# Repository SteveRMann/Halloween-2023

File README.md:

## PrizeDelivery
This repository contains the files for the Halloween prize delivery mechanism.

The mechanism is a rotisserie motor that rotates on command (a button press).
Once started, the motor continues until a "home" microswitch is closed.
Because the motor is slow, like 20 seconds for 360°, the "home" position is 
just before a drop would occur.

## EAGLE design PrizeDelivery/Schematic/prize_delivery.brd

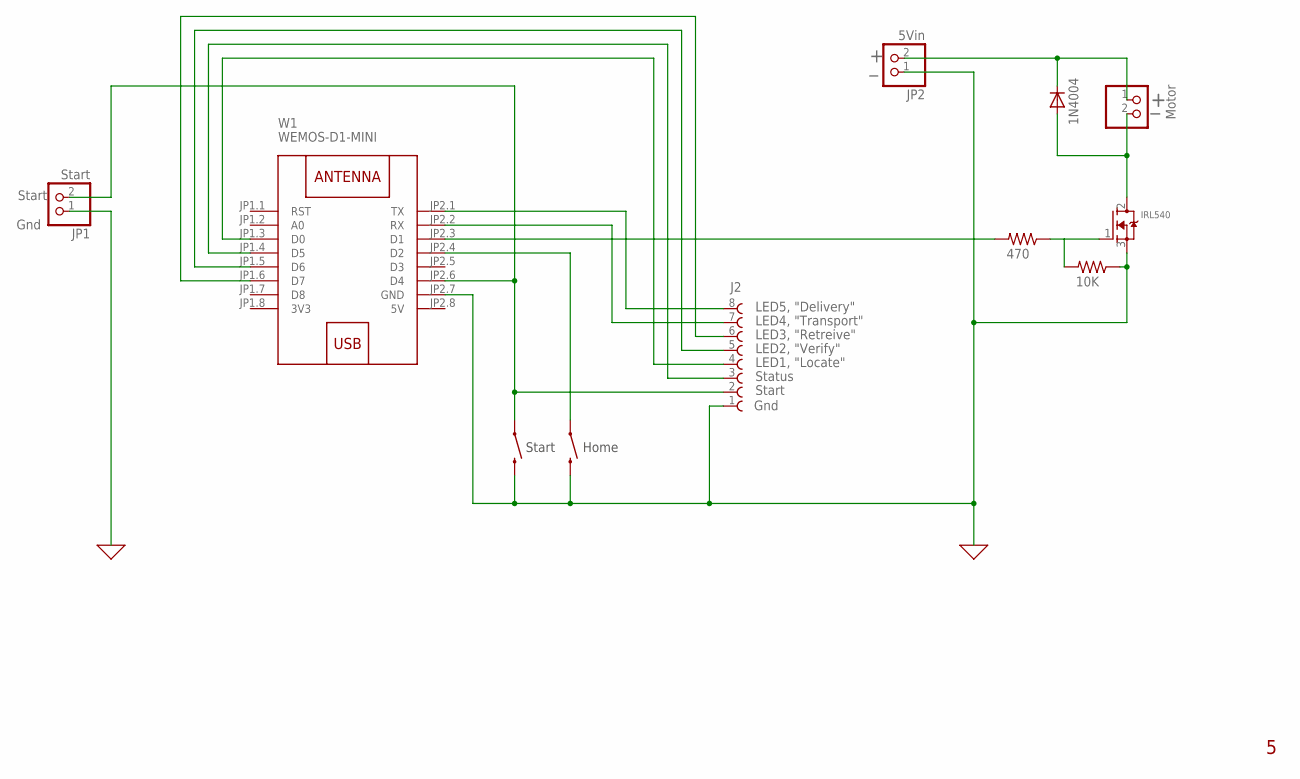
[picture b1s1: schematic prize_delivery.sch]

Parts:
360°: MOMENTARY-SWITCH-SPST-PTH-6.0MM; TACTILE_SWITCH_PTH_6.0MM
D1: 1N4004; DO41-10
J2: 691136710008
JP1: Start; 1X02
JP2: 5Vin; 1X02
JP3: Motor; 1X02
Q1: IRL540; TO220V
R2: 470; 0207/10
R4: 10K; 0207/10
START: MOMENTARY-SWITCH-SPST-PTH-6.0MM; TACTILE_SWITCH_PTH_6.0MM
W1: WEMOS-D1-MINI

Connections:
0: 360°.3 (2), J2.1, JP1.1, JP2.1, Q1.3 (S), R4.1, START.3 (2), W1.JP2.7 (GND)
3V3: W1.JP1.8 (3V3)
5V: W1.JP2.8 (5V)
unnamed: D1.A, JP3.2, Q1.2 (D)
unnamed: D1.C, JP2.2, JP3.1
unnamed: 360°.1, W1.JP2.4 (D2)
unnamed: R2.2, W1.JP2.3 (D1)
unnamed: J2.2, JP1.2, START.1, W1.JP2.6 (D4)
unnamed: Q1.1 (G), R2.1, R4.2
unnamed: J2.4, W1.JP1.3 (D0)
unnamed: J2.5, W1.JP1.5 (D6)
unnamed: J2.6, W1.JP1.6 (D7)
unnamed: J2.8, W1.JP2.1 (TX)
unnamed: J2.7, W1.JP2.2 (RX)
unnamed: J2.3, W1.JP1.4 (D5)

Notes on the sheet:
Home
Start
Gnd
LED1, "Locate"
LED2, "Verify"
LED3, "Retreive"
LED4, "Transport"
LED5, "Delivery"
Status

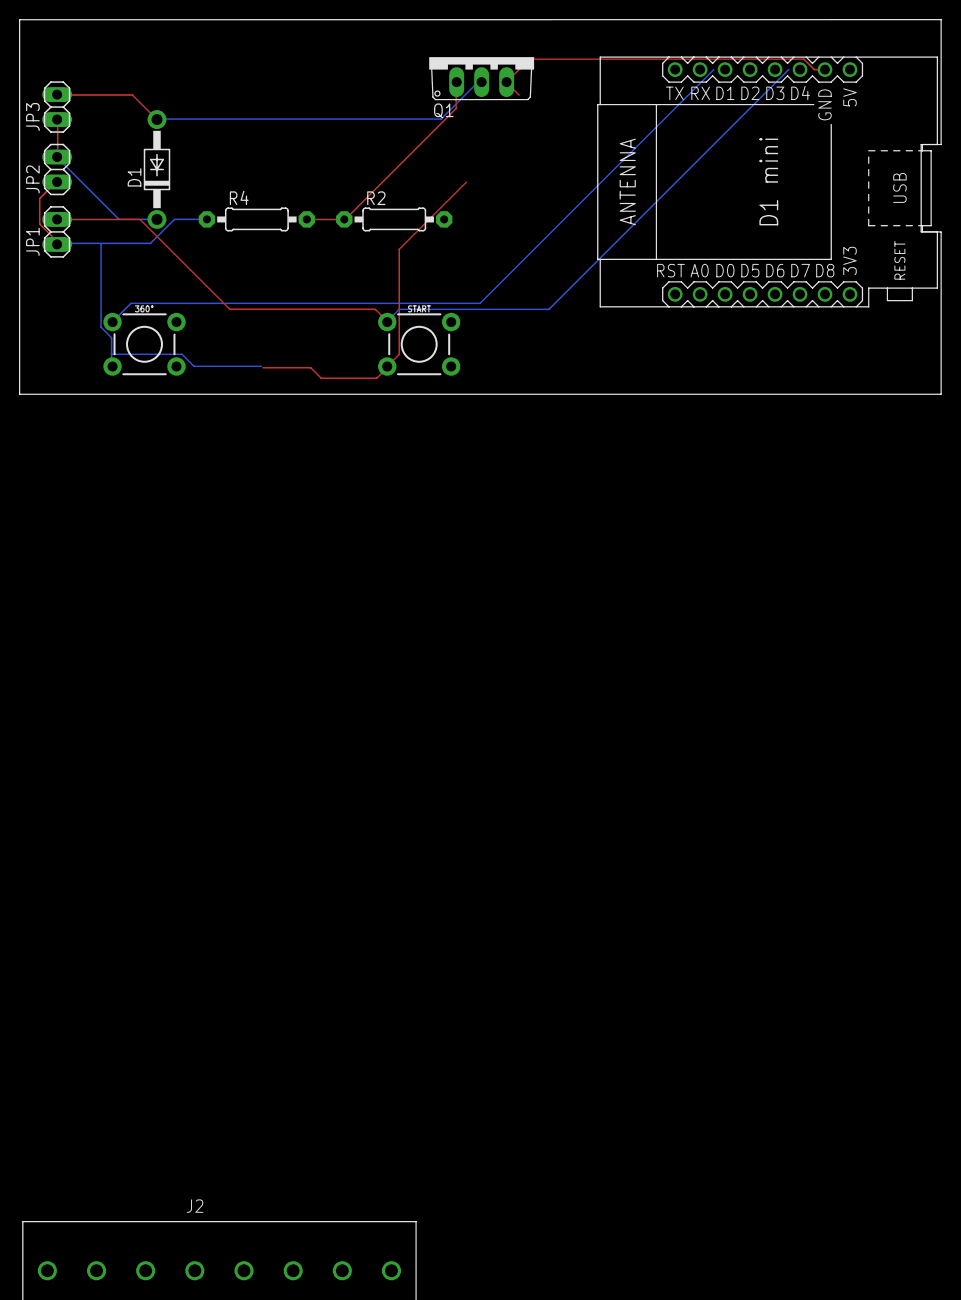
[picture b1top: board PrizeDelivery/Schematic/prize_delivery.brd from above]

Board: 2 copper layers, 93.7 x 38.1 mm, 11 parts (0 on the bottom side), 13 nets.

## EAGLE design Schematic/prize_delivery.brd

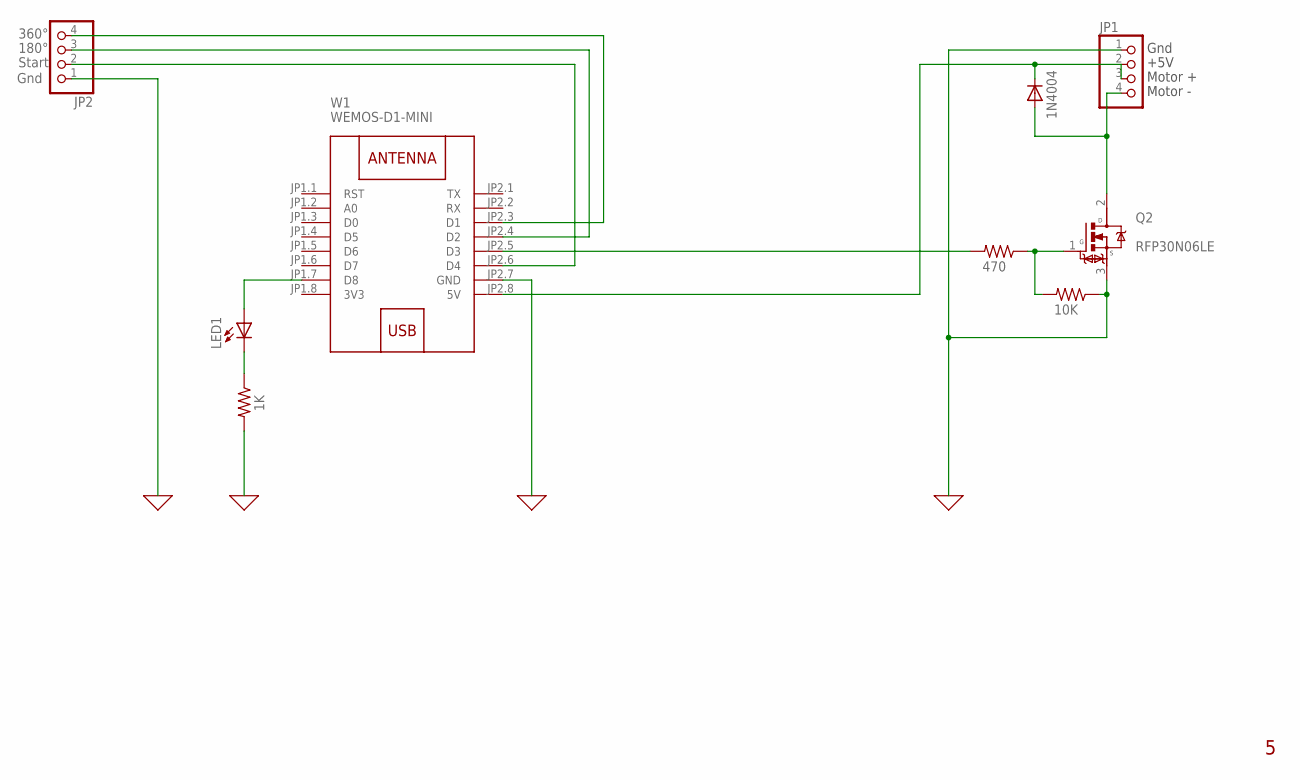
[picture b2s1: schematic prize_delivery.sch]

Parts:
D1: 1N4004; DO41-10
JP1, JP2: PINHD-1X4; 1X04
LED1: LED5MM
Q2: RFP30N06LE; TRANS_RFP30N06LE
R1: 1K; 0207/10
R2: 470; 0207/10
R4: 10K; 0207/10
W1: WEMOS-D1-MINI

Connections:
0: JP1.1, JP2.1, Q2.3 (S), R1.2, R4.1, W1.JP2.7 (GND)
3V3: W1.JP1.8 (3V3)
unnamed: R2.2, W1.JP2.5 (D3)
unnamed: D1.A, JP1.4, Q2.2 (D)
unnamed: D1.C, JP1.2, JP1.3, W1.JP2.8 (5V)
unnamed: JP2.3, W1.JP2.4 (D2)
unnamed: JP2.4, W1.JP2.3 (D1)
unnamed: LED1.A, W1.JP1.7 (D8)
unnamed: LED1.K (C), R1.1
unnamed: Q2.1 (G), R2.1, R4.2
unnamed: JP2.2, W1.JP2.6 (D4)

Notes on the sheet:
Gnd
Start
180°
360°
Motor +
Motor -
+5V

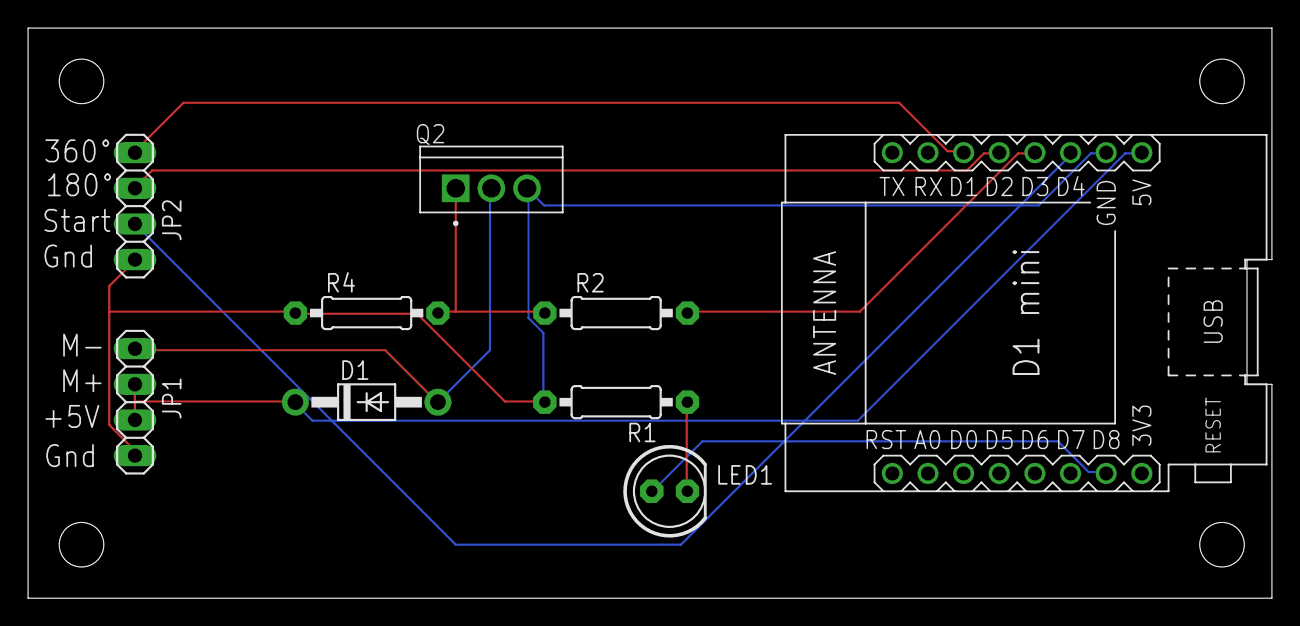
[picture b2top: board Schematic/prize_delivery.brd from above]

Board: 2 copper layers, 88.6 x 40.6 mm, 9 parts (0 on the bottom side), 10 nets.

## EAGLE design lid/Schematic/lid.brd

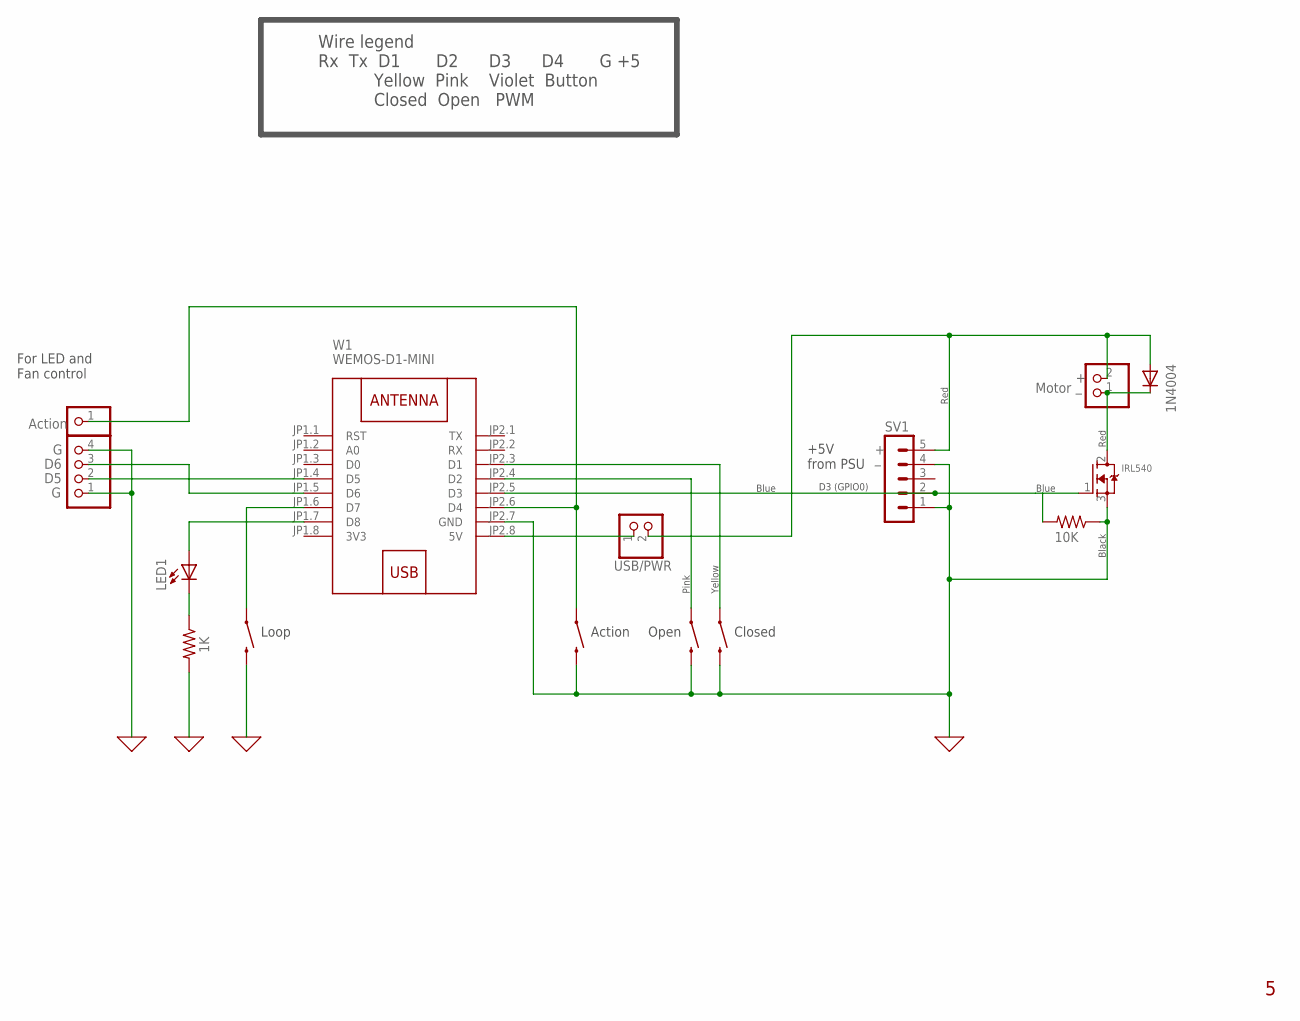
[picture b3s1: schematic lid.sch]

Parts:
ACTION, ACTION1: MOMENTARY-SWITCH-SPST-PTH-6.0MM; TACTILE_SWITCH_PTH_6.0MM
D1: 1N4004; DO41-10
JP1: PINHD-1X1; 1X01
JP3: PINHD-1X2; 1X02
JP4: PINHD-1X4; 1X04
LED1: LED5MM
Q1: IRL540; TO220V
R1: 1K; 0207/10
R4: 10K; 0207/10
S1, S2: MOMENTARY-SWITCH-SPST-PTH-6.0MM; TACTILE_SWITCH_PTH_6.0MM
SV1: MA05-1
USB/PWR: PINHD-1X2; 1X02
W1: WEMOS-D1-MINI

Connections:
0: ACTION.3 (2), ACTION1.3 (2), JP4.1, JP4.4, Q1.3 (S), R1.2, R4.1, S1.3 (2), S2.3 (2), SV1.1, SV1.4, W1.JP2.7 (GND)
3V3: W1.JP1.8 (3V3)
unnamed: Q1.1 (G), R4.2, SV1.2, W1.JP2.5 (D3)
unnamed: D1.C, JP3.1, Q1.2 (D)
unnamed: D1.A, JP3.2, SV1.5, USB/PWR.2
unnamed: S1.1, W1.JP2.4 (D2)
unnamed: S2.1, W1.JP2.3 (D1)
unnamed: LED1.A, W1.JP1.7 (D8)
unnamed: LED1.K (C), R1.1
unnamed: USB/PWR.1, W1.JP2.8 (5V)
unnamed: ACTION.1, JP1.1, W1.JP2.6 (D4)
unnamed: JP4.2, W1.JP1.4 (D5)
unnamed: JP4.3, W1.JP1.5 (D6)
unnamed: ACTION1.1, W1.JP1.6 (D7)

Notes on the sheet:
Motor
+5V from PSU
D3 (GPIO0)
Open
Closed
Yellow
Pink
Blue
Black
Red
Action
Wire legend Rx Tx D1 D2 D3 D4 G +5 Yellow Pink Violet Button Closed Open PWM
For LED and Fan control
Loop

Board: 2 copper layers, 15 parts (0 on the bottom side), 13 nets, no tracks yet.

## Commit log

2023-06-13 New repository
2023-06-14 Cleaning up filenames
2023-06-14 Removed lid
2023-06-15 Commented out mqtt stuff
2023-06-15 Lots of rewtire
2023-06-16 Update schematic
2023-06-16 Crap
2023-06-17 Pause at 180 then continue to 360.
2023-06-17 Modified schematic
2023-06-17 Update PCB
2023-06-18 Cleanup
2023-06-18 Bumped start_button debounce to 300ms
2023-06-19 Added ESPHome yaml file
2023-06-20 Switch hardware to D1 Mini Relay Shield
2023-06-20 Removed Prize2
2023-06-29 Reconstruct the schematic and board files
2023-08-13 New folders
2023-08-27 Added images folder
2024-05-11 Not sure
2024-05-11 Added Fred's Chair YAML file

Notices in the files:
parts and their libraries:
SparkFun-Switches: Licensing: Creative Commons ShareAlike 4.0 International - https://creativecommons.org/licenses/by-sa/4.0
diy-modules: Released under the Creative Commons Attribution 4.0 International License: http://creativecommons.org/licenses/by/4.0
